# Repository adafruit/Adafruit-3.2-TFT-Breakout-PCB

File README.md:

## Adafruit 3.2" TFT LCD with Touchscreen Breakout Board w/MicroSD Socket - ILI9341 PCB

<a href="http://www.adafruit.com/products/1743"><br/>
Click here to purchase one from the Adafruit shop</a>

PCB files for the Adafruit 3.2" TFT LCD with Touchscreen Breakout Board w/MicroSD Socket - ILI9341. 

Format is EagleCAD schematic and board layout
* https://www.adafruit.com/product/1743

### Description

Add some jazz & pizazz to your project with a color touchscreen LCD. This TFT display is really big (3.2" diagonal) bright (6 white-LED backlight) and colorful! 240x320 pixels with individual RGB pixel control, this has way more resolution than a black and white 128x64 display. As a bonus, this display has a resistive touchscreen attached to it already, so you can detect finger presses anywhere on the screen.

This display has a controller built into it with RAM buffering, so that almost no work is done by the microcontroller. The display can be used in two modes: 8-bit and SPI. For 8-bit mode, you'll need 8 digital data lines and 4 or 5 digital control lines to read and write to the display (12 lines total). SPI mode requires only 5 pins total (SPI data in, data out, clock, select, and d/c) but is slower than 8-bit mode. In addition, 4 pins are required for the touch screen (2 digital, 2 analog) or you can purchase and use our resistive touchscreen controller (not included) to use I2C or SPI

We wrapped up this display into an easy-to-use breakout board, with SPI connections on one end and 8-bit on the other. Both are 3-5V compliant with high-speed level shifters so you can use with any microcontroller. If you're going with SPI mode, you can also take advantage of the onboard MicroSD card socket to display images. (microSD card not included, but any will work)

Of course, we wouldn't just leave you with a datasheet and a "good luck!". For 8-bit interface fans we've written a full open source graphics library that can draw pixels, lines, rectangles, circles, text, and more. For SPI users, we have a library as well, its separate from the 8-bit library since both versions are heavily optimized. We also have a touch screen library that detects x, y and z (pressure) and example code to demonstrate all of it.

[Follow our step by step guide for wiring, code and drawing. You'll be running in 15 minutes](https://learn.adafruit.com/adafruit-2-8-and-3-2-color-tft-touchscreen-breakout-v2)

### License

Adafruit invests time and resources providing this open source design, please support Adafruit and open-source hardware by purchasing products from [Adafruit](https://www.adafruit.com)!

Designed by Limor Fried/Ladyada for Adafruit Industries.

Creative Commons Attribution/Share-Alike, all text above must be included in any redistribution. 
See license.txt for additional details.

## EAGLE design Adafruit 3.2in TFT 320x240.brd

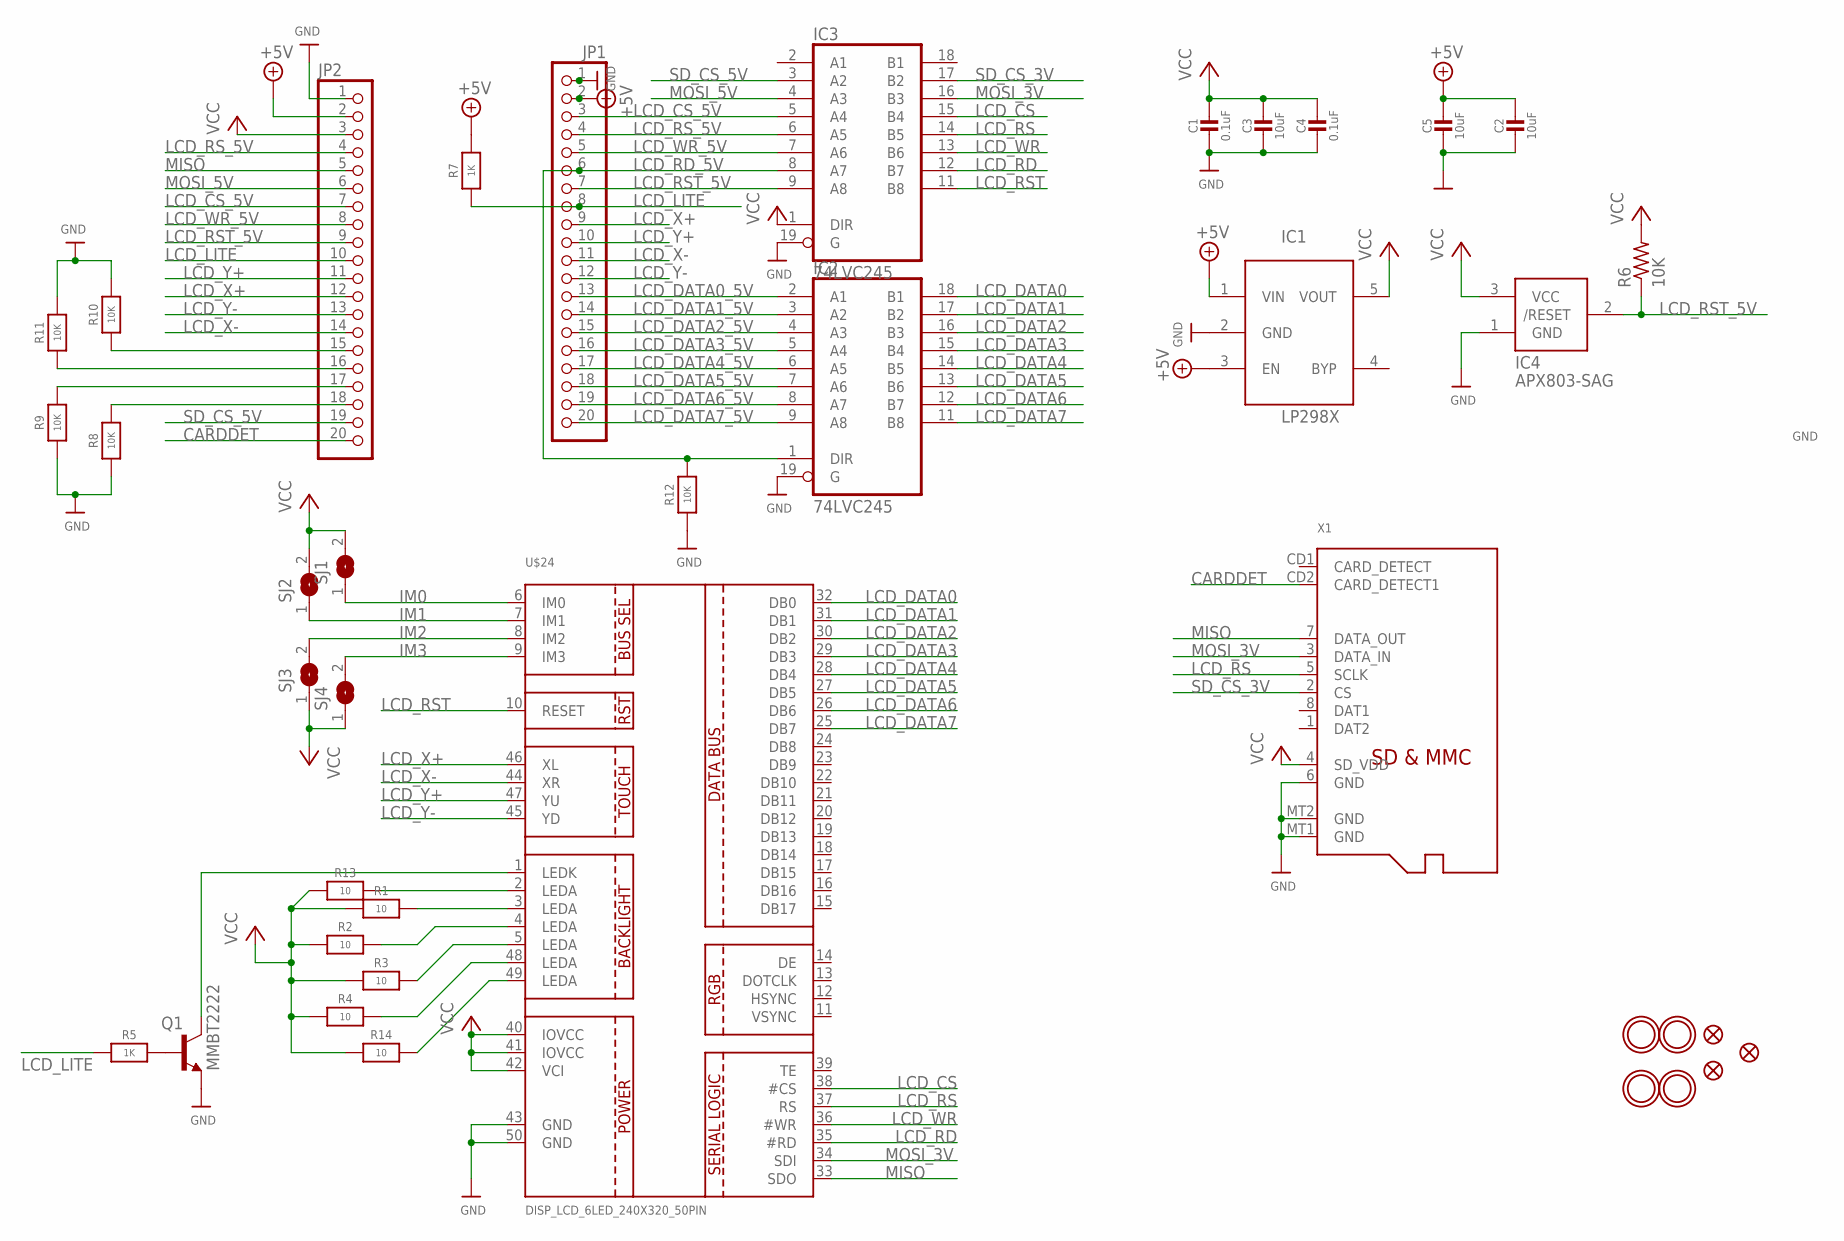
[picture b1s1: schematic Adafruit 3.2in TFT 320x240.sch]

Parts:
C1, C4: 0.1uF; 0805-NO
C2, C3, C5: 10uF; 0805-NO
IC1: APA2112-3.3; SOT23-5L
IC2, IC3: 74LVC245; SO20W
IC4: APX803-SAG; SOT23
JP1, JP2: HEADER-1X20ROUND; 1X20_ROUND
Q1: MMBT2222; SOT23-BEC
R1, R2, R3, R4, R13, R14: 10; 0805-NO
R5, R7: 1K; 0805-NO
R6: 10K; R0805
R8, R9, R10, R11, R12: 10K; 0805-NO
SJ1, SJ2, SJ3, SJ4: SOLDERJUMPER; SOLDERJUMPER_ARROW_NOPASTE
U$7, U$15, U$16, U$17: MOUNTINGHOLE3.0THIN; MOUNTINGHOLE_3.0_PLATEDTHIN
U$9, U$11, U$23: FIDUCIAL""; FIDUCIAL_1MM
U$24: DISP_LCD_6LED_240X320_50PIN; TFT_3.2IN_240X320_50PIN
X1: MICROSD

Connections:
+5V: C2.1, C5.1, IC1.1 (VIN), IC1.3 (EN), JP1.2, JP2.2, R7.2
CARDDET: JP2.20, X1.CD2 (CARD_DETECT1)
GND: C1.2, C2.2, C3.2, C4.2, C5.2, IC1.2 (GND), IC2.10 (GND), IC2.19 (G), IC3.10 (GND), IC3.19 (G), IC4.1 (GND), JP1.1, JP2.1, Q1.E, R8.1, R9.1, R10.2, R11.2, R12.1, U$24.43 (GND), U$24.50 (GND), X1.6 (GND), X1.MT1 (GND), X1.MT2 (GND)
IM0: JP2.18, R8.2, SJ1.1, U$24.6 (IM0)
IM1: JP2.17, R9.2, SJ2.1, U$24.7 (IM1)
IM2: JP2.16, R11.1, SJ3.2, U$24.8 (IM2)
IM3: JP2.15, R10.1, SJ4.2, U$24.9 (IM3)
LCD_CS: IC3.15 (B4), U$24.38 (#CS)
LCD_CS_5V: IC3.5 (A4), JP1.3, JP2.7
LCD_DATA0: IC2.18 (B1), U$24.32 (DB0)
LCD_DATA0_5V: IC2.2 (A1), JP1.13
LCD_DATA1: IC2.17 (B2), U$24.31 (DB1)
LCD_DATA1_5V: IC2.3 (A2), JP1.14
LCD_DATA2: IC2.16 (B3), U$24.30 (DB2)
LCD_DATA2_5V: IC2.4 (A3), JP1.15
LCD_DATA3: IC2.15 (B4), U$24.29 (DB3)
LCD_DATA3_5V: IC2.5 (A4), JP1.16
LCD_DATA4: IC2.14 (B5), U$24.28 (DB4)
LCD_DATA4_5V: IC2.6 (A5), JP1.17
LCD_DATA5: IC2.13 (B6), U$24.27 (DB5)
LCD_DATA5_5V: IC2.7 (A6), JP1.18
LCD_DATA6: IC2.12 (B7), U$24.26 (DB6)
LCD_DATA6_5V: IC2.8 (A7), JP1.19
LCD_DATA7: IC2.11 (B8), U$24.25 (DB7)
LCD_DATA7_5V: IC2.9 (A8), JP1.20
LCD_LITE: JP1.8, JP2.10, R5.1, R7.1
LCD_RD: IC3.12 (B7), U$24.35 (#RD)
LCD_RD_5V: IC2.1 (DIR), IC3.8 (A7), JP1.6, R12.2
LCD_RS: IC3.14 (B5), U$24.37 (RS), X1.5 (SCLK)
LCD_RST: IC3.11 (B8), U$24.10 (RESET)
LCD_RST_5V: IC3.9 (A8), IC4.2 (/RESET), JP1.7, JP2.9, R6.1
LCD_RS_5V: IC3.6 (A5), JP1.4, JP2.4
LCD_WR: IC3.13 (B6), U$24.36 (#WR)
LCD_WR_5V: IC3.7 (A6), JP1.5, JP2.8
LCD_X+: JP1.9, JP2.12, U$24.46 (XL)
LCD_X-: JP1.11, JP2.14, U$24.44 (XR)
LCD_Y+: JP1.10, JP2.11, U$24.47 (YU)
LCD_Y-: JP1.12, JP2.13, U$24.45 (YD)
MISO: JP2.5, U$24.33 (SDO), X1.7 (DATA_OUT)
MOSI_3V: IC3.16 (B3), U$24.34 (SDI), X1.3 (DATA_IN)
MOSI_5V: IC3.4 (A3), JP2.6
unnamed: R4.2, U$24.48 (LEDA)
unnamed: R1.2, U$24.3 (LEDA)
unnamed: R2.2, U$24.4 (LEDA)
unnamed: R3.2, U$24.5 (LEDA)
unnamed: Q1.C, U$24.1 (LEDK)
unnamed: R14.2, U$24.49 (LEDA)
unnamed: R13.2, U$24.2 (LEDA)
unnamed: Q1.B, R5.2
SD_CS_3V: IC3.17 (B2), X1.2 (CS)
SD_CS_5V: IC3.3 (A2), JP2.19
VCC: C1.1, C3.1, C4.1, IC1.5 (VOUT), IC2.20 (VCC), IC3.1 (DIR), IC3.20 (VCC), IC4.3 (VCC), JP2.3, R1.1, R2.1, R3.1, R4.1, R6.2, R13.1, R14.1, SJ1.2, SJ2.2, SJ3.1, SJ4.1, U$24.40 (IOVCC), U$24.41 (IOVCC), U$24.42 (VCI), X1.4 (SD_VDD)

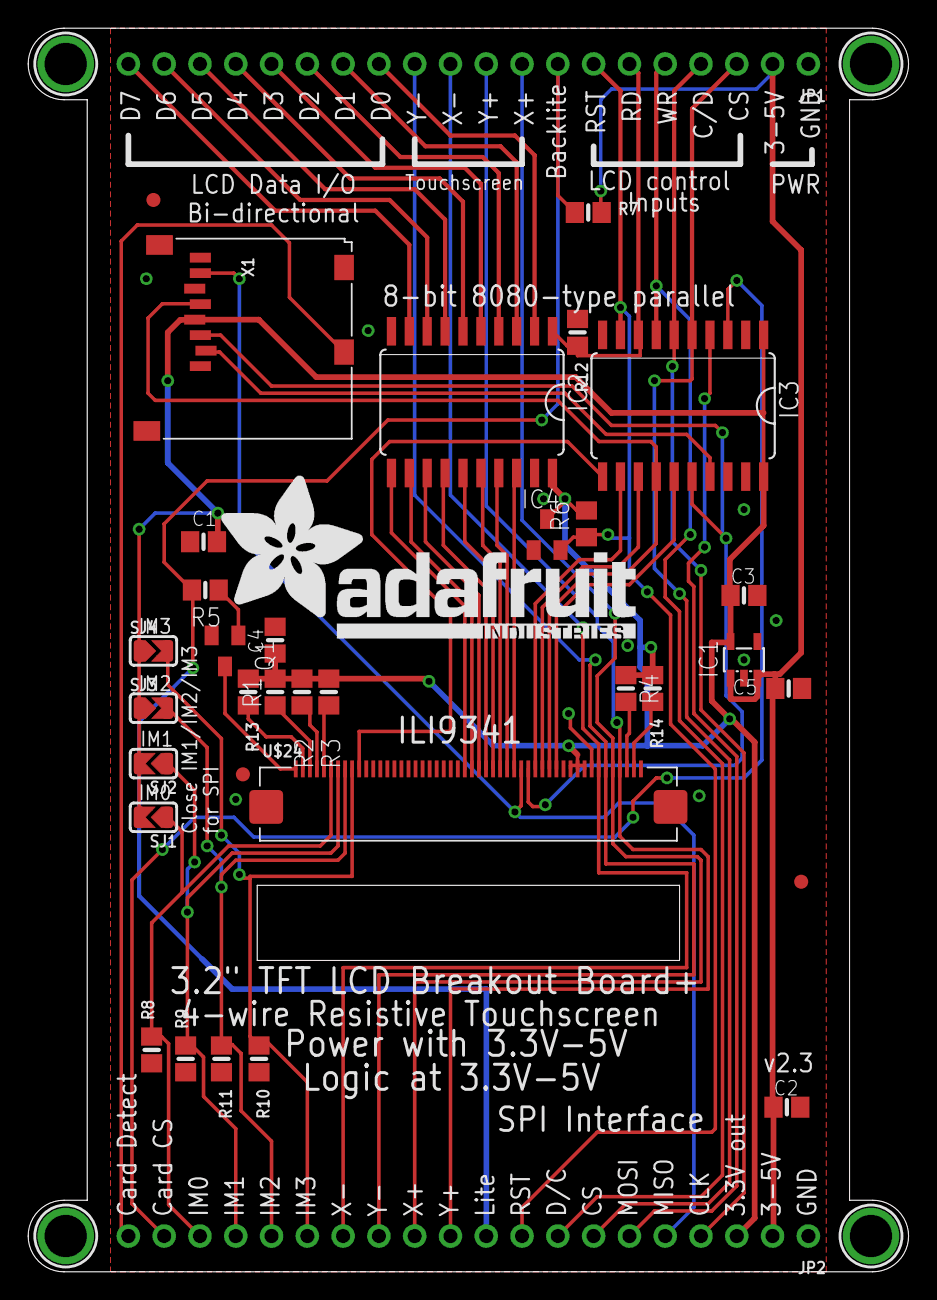
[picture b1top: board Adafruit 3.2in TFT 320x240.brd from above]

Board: 2 copper layers, 62.5 x 88.3 mm, 40 parts (1 on the bottom side), 52 nets.

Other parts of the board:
U$19: ADAFRUIT_TEXT_30MM

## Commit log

2021-08-13 Added project copy
2021-08-13 Rename Adafruit 3.2in 320x240.brd to Adafruit 3.2in TFT 320x240.brd
2021-08-13 Rename Adafruit 3.2in 320x240.sch to Adafruit 3.2in TFT 320x240.sch
